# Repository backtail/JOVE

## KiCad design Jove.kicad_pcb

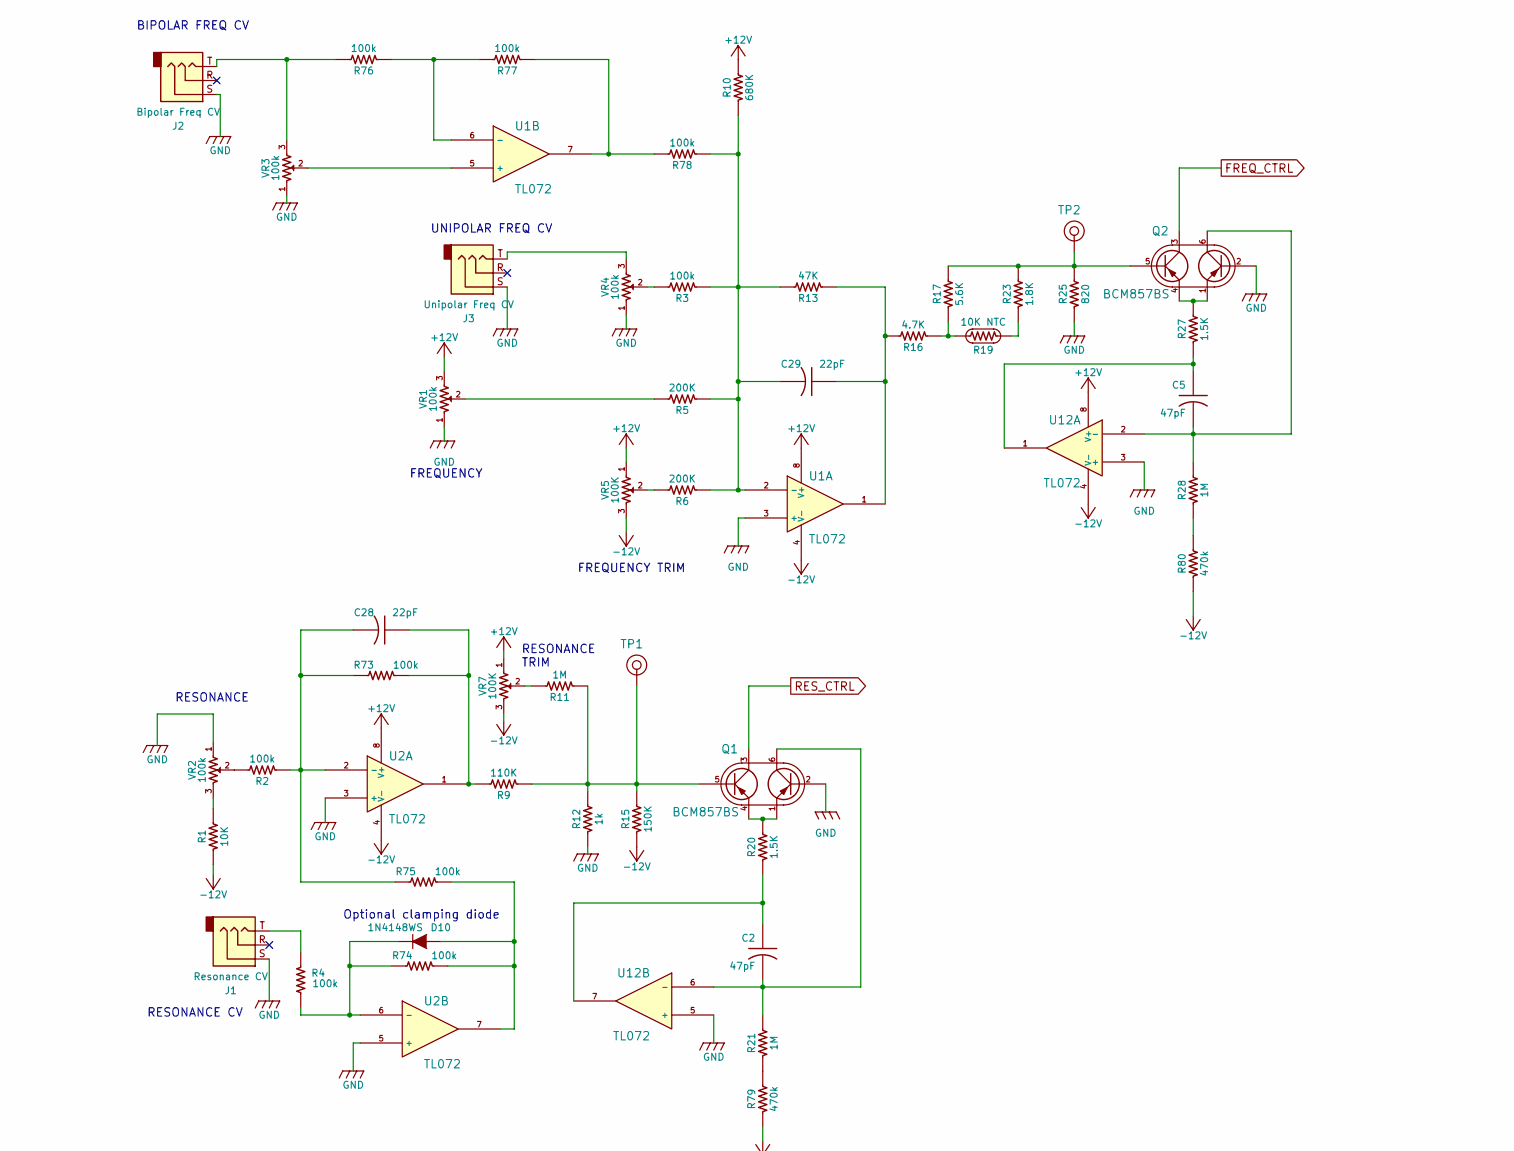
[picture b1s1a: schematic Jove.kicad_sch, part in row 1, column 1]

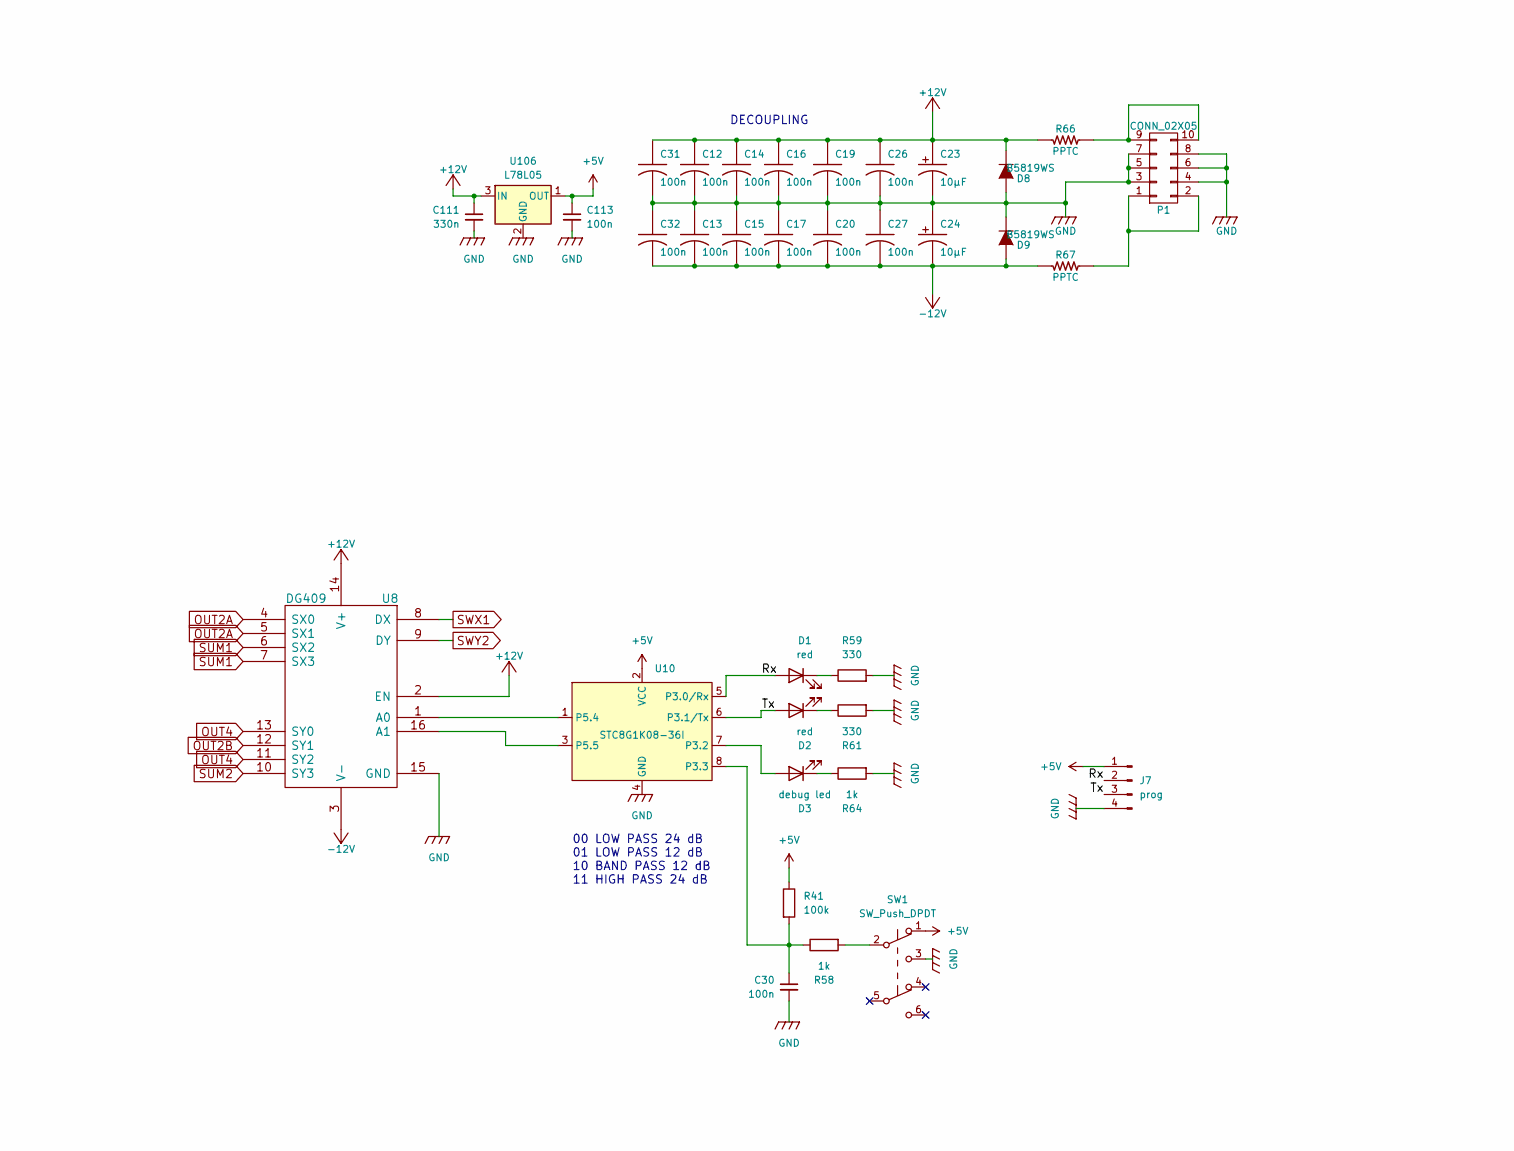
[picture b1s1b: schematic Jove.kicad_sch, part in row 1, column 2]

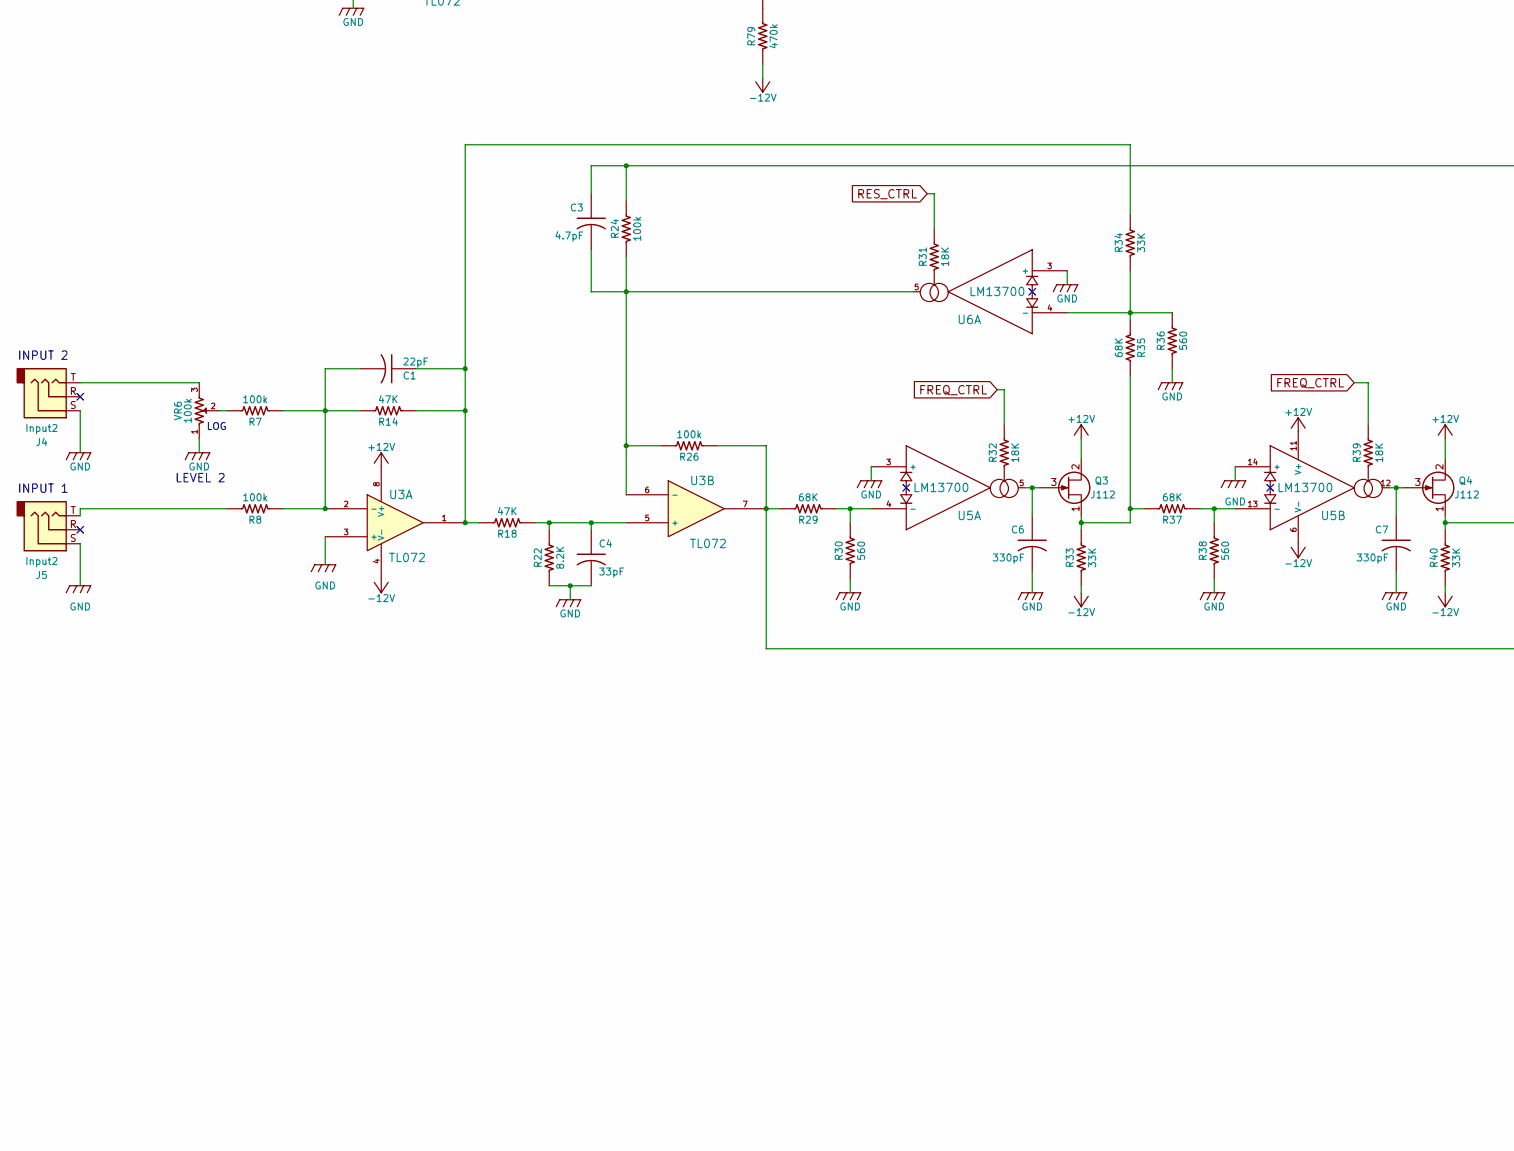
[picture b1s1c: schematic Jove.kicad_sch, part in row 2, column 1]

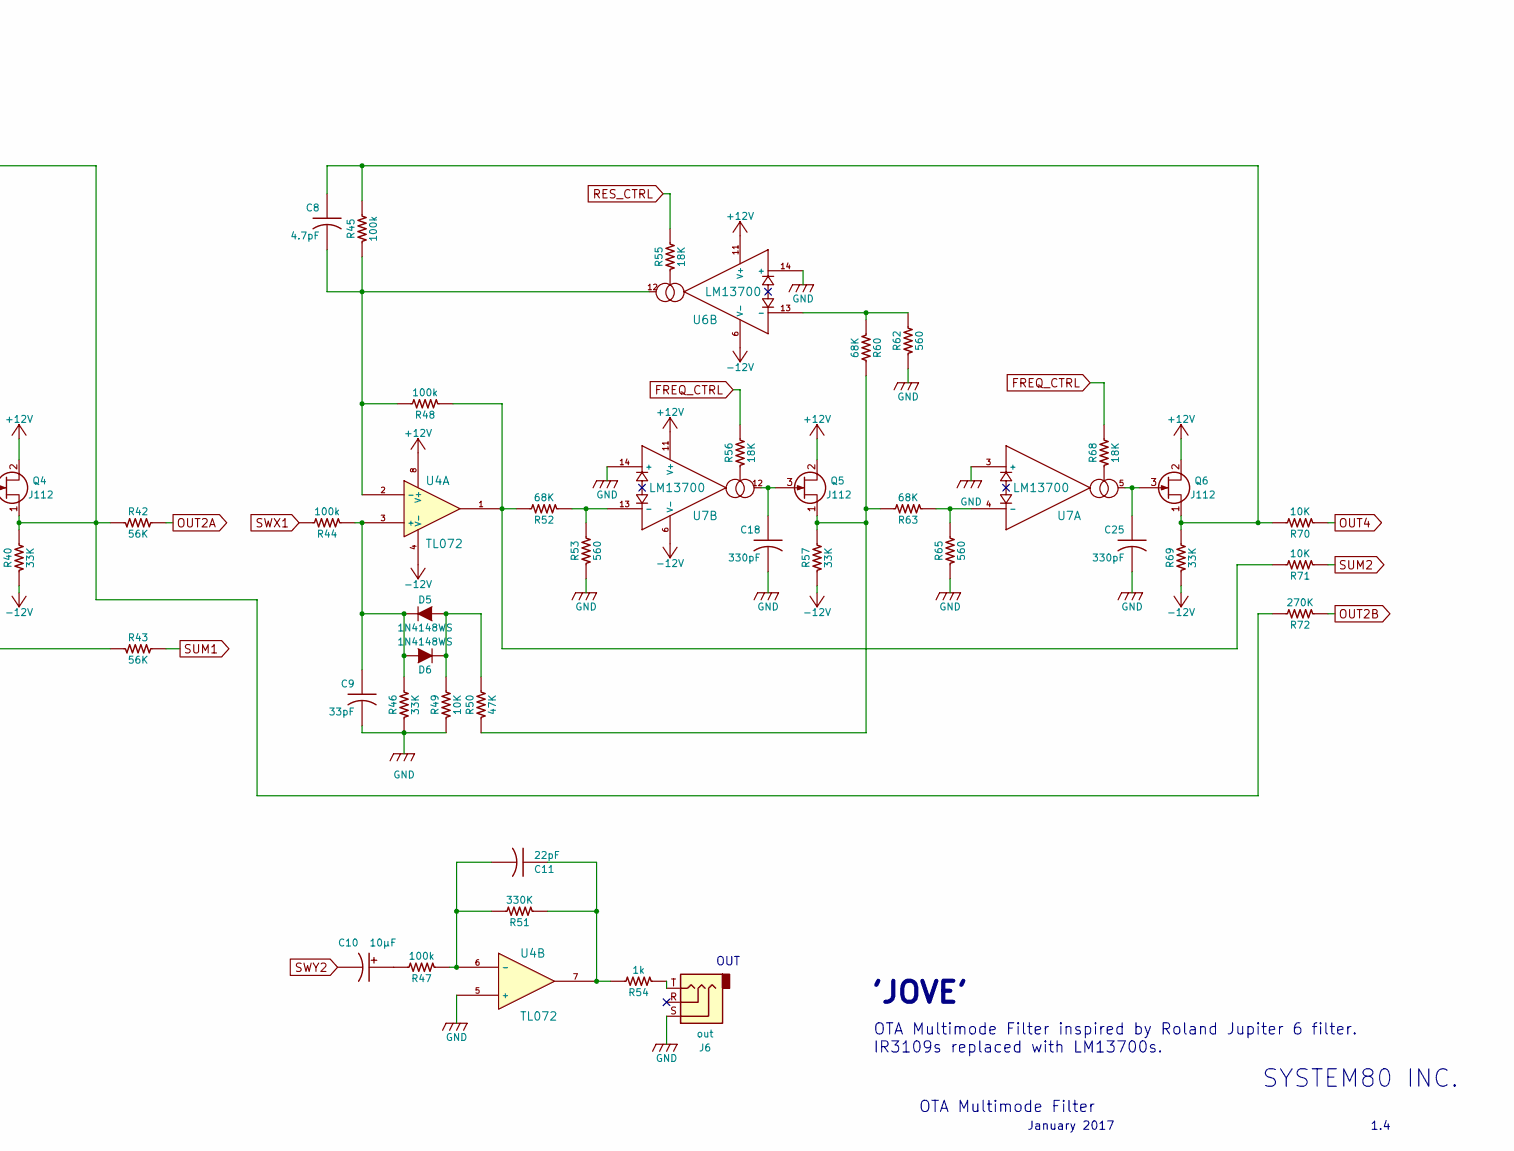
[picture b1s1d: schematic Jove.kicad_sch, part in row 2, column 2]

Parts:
C1, C11, C28, C29: 22pF; C_0603_1608Metric; LCSC Part # C1653
C2, C5: 47pF; C_0603_1608Metric; LCSC Part # C1671
C3, C8: 4.7pF; C_0603_1608Metric; LCSC Part # C1669
C4, C9: 33pF; C_0603_1608Metric; LCSC Part # C1663
C6, C7, C18, C25: 330pF; C_0603_1608Metric; LCSC Part # C1664
C10, C23, C24: 10μF; CP_EIA-3216-18_Kemet-A; LCSC Part # C7171
C12, C13, C14, C15, C16, C17, C19, C20, C26, C27, C30, C31, C32, C113: 100n; C_0402_1005Metric; LCSC Part # C1525
C111: 330n; C_0603_1608Metric; LCSC Part # C1615
D1, D2: red; LED_D1.8mm_W3.3mm_H2.4mm
D3: debug led; D_0603_1608Metric; LCSC Part # C2286
D5, D6, D10: 1N4148WS; D_SOD-323; LCSC Part # C2128
D8, D9: B5819WS; D_SOD-323; LCSC Part # C7420331
J1: Resonance CV; Jack_3.5mm_PJ392_Vertical
J2: Bipolar Freq CV; Jack_3.5mm_PJ392_Vertical
J3: Unipolar Freq CV; Jack_3.5mm_PJ392_Vertical
J4, J5: Input2; Jack_3.5mm_PJ392_Vertical
J6: out; Jack_3.5mm_PJ392_Vertical
J7: prog; PinHeader_1x04_P2.54mm_Vertical
P1: CONN_02X05; Eurorack_10Pin; LCSC Part # C5383106
Q1, Q2: BCM857BS; SOT-363_SC-70-6; LCSC Part # C105887
Q3, Q4, Q5, Q6: J112; SOT-23; LCSC Part # C258195
R1, R49, R70, R71: 10K; R_0603_1608Metric; LCSC Part # C25804
R2, R3, R4, R7, R8, R24, R26, R41, R44, R45, R47, R48, R73, R74, R75, R76, R77, R78: 100k; R_0603_1608Metric; LCSC Part # C25803
R5, R6: 200K; R_0603_1608Metric; LCSC Part # C25811
R9: 110K; R_0603_1608Metric; LCSC Part # C25805
R10: 680K; R_0603_1608Metric; LCSC Part # C25822
R11, R21, R28: 1M; R_0603_1608Metric; LCSC Part # C22935
R12, R54, R58, R64: 1k; R_0603_1608Metric; LCSC Part # C21190
R13, R14, R18, R50: 47K; R_0603_1608Metric; LCSC Part # C25819
R15: 150K; R_0603_1608Metric; LCSC Part # C22807
R16: 4.7K; R_0603_1608Metric; LCSC Part # C23162
R17: 5.6K; R_0603_1608Metric; LCSC Part # C23189
R19: 10K NTC; R_0805_2012Metric; LCSC Part # C25804
R20, R27: 1.5K; R_0603_1608Metric; LCSC Part # C22843
R22: 8.2K; R_0603_1608Metric; LCSC Part # C25981
R23: 1.8K; R_0603_1608Metric; LCSC Part # C4177
R25: 820; R_0603_1608Metric; LCSC Part # C23253
R29, R35, R37, R52, R60, R63: 68K; R_0603_1608Metric; LCSC Part # C23231
R30, R36, R38, R53, R62, R65: 560; R_0603_1608Metric; LCSC Part # C23204
R31, R32, R39, R55, R56, R68: 18K; R_0603_1608Metric; LCSC Part # C25810
R33, R34, R40, R46, R57, R69: 33K; R_0603_1608Metric; LCSC Part # C4216
R42, R43: 56K; R_0603_1608Metric; LCSC Part # C23206
R51: 330K; R_0603_1608Metric; LCSC Part # C23137
R59, R61: 330; R_0603_1608Metric; LCSC Part # C23138
R66, R67: PPTC; R_1206_3216Metric; LCSC Part # C2649905
R72: 270K; R_0603_1608Metric; LCSC Part # C22965
R79, R80: 470k; R_0603_1608Metric; LCSC Part # C23178
SW1: SW_Push_DPDT; SW_5.8x5.8mm
TP1, TP2: TEST_POINT; TestPoint_Pad_2.5x2.5mm
U1, U2, U3, U4, U12: TL072; SOIC-8_3.9x4.9mm_P1.27mm; LCSC Part # C6961
U5, U6, U7: LM13700; SOIC-16_3.9x9.9mm_P1.27mm; LCSC Part # C521166
U8: DG409; SOIC-16_3.9x9.9mm_P1.27mm; LCSC Part # C142533
U10: STC8G1K08-36I; SOIC-8_3.9x4.9mm_P1.27mm; LCSC Part # C713818
U106: L78L05; SOT-89-3; LCSC Part # C71136
VR1, VR2, VR3, VR4, VR6: 100k; Potentiometer_RK09_RV09_Vertical
VR5, VR7: 100K; Potentiometer_Bourns_TC33X_Vertical; LCSC Part # C128545

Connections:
+5V: J7.1, R41.1, SW1.1 (A), U10.2 (VCC); also elsewhere on the board
+12V: C12.1, C14.1, C16.1, C19.1, C23.1 (+), C26.1, C31.1, D8.1 (K), Q3.2 (D), Q4.2 (D), Q5.2 (D), Q6.2 (D), R10.2, R66.1, U1.8 (V+), U2.8 (V+), U3.8 (V+), U4.8 (V+), U5.11 (V+), U6.11 (V+), U7.11 (V+), U8.2 (EN), U8.14 (V+), U12.8 (V+), VR1.3, VR5.1, VR7.1; also elsewhere on the board
-12V: C13.2, C15.2, C17.2, C20.2, C24.2 (-), C27.2, C32.2, D9.2 (A), R1.2, R15.2, R33.1, R40.1, R57.1, R67.1, R69.1, R79.2, R80.2, U1.4 (V-), U2.4 (V-), U3.4 (V-), U4.4 (V-), U5.6 (V-), U6.6 (V-), U7.6 (V-), U8.3 (V-), U12.4 (V-), VR5.3, VR7.3
/Rx: D1.2 (A), J7.2, U10.5 (P3.0/Rx)
/Tx: D2.2 (A), J7.3, U10.6 (P3.1/Tx)
FREQ_CTRL: Q2.3 (C2), R32.2, R39.2, R56.2, R68.2
GND: C4.2, C6.2, C7.2, C9.2, C12.2, C13.1, C14.2, C15.1, C16.2, C17.1, C18.2, C19.2, C20.1, C23.2 (-), C24.1 (+), C25.2, C26.2, C27.1, C30.2, C31.2, C32.1, D8.2 (A), D9.1 (K), J1.S, J2.S, J3.S, J4.S, J5.S, J6.S, J7.4, P1.3, P1.4, P1.5, P1.6, P1.7, P1.8, Q1.2 (B1), Q2.2 (B1), R12.2, R22.1, R25.1, R30.1, R36.1, R38.1, R46.1, R49.1, R53.1, R59.2, R61.2, R62.1, R64.2, R65.1, SW1.3 (C), U1.3 (+), U2.3 (+), U2.5 (+), U3.3 (+), U4.5 (+), U5.3 (+), U5.14 (+), U6.3 (+), U6.14 (+), U7.3 (+), U7.14 (+), U8.15 (GND), U10.4 (GND), U12.3 (+), U12.5 (+), VR1.1, VR2.1, VR3.1, VR4.1, VR6.1; also elsewhere on the board
unnamed: C1.1, R14.1, R18.2, R34.2, U3.1
unnamed: C2.1, R20.2, U12.7
unnamed: C5.1, R27.2, U12.1
unnamed: C10.1 (+), R47.2
unnamed: C11.1, R51.1, R54.2, U4.7
unnamed: C28.1, R9.2, R73.1, U2.1
unnamed: C29.1, R13.1, R16.2, U1.1
unnamed: D1.1 (K), R59.1
unnamed: D2.1 (K), R61.1
unnamed: D3.2 (A), U10.7 (P3.2)
unnamed: D3.1 (K), R64.1
unnamed: D5.2 (A), D6.1 (K), R49.2, R50.2
unnamed: C9.1, D5.1 (K), D6.2 (A), R44.1, R46.2, U4.3 (+)
unnamed: D10.2 (A), R74.1, R75.1, U2.7
unnamed: D10.1 (K), R4.1, R74.2, U2.6 (-)
unnamed: J1.T, R4.2
unnamed: J2.T, R76.2, VR3.3
unnamed: J3.T, VR4.3
unnamed: J4.T, VR6.3
unnamed: J5.T, R8.2
unnamed: J6.T, R54.1
unnamed: P1.1, P1.2, R67.2
unnamed: P1.9, P1.10, R66.2
unnamed: Q1.5 (B2), R9.1, R11.1, R12.1, R15.1, TP1.1
unnamed: C2.2, Q1.6 (C1), R21.1, U12.6 (-)
unnamed: Q1.1 (E1), Q1.4 (E2), R20.1
unnamed: Q2.5 (B2), R17.2, R23.2, R25.2, TP2.1
unnamed: C5.2, Q2.6 (C1), R28.1, U12.2 (-)
unnamed: Q2.1 (E1), Q2.4 (E2), R27.1
unnamed: C6.1, Q3.3 (G), U5.5
unnamed: Q3.1 (S), R33.2, R35.2, R37.2
unnamed: C7.1, Q4.3 (G), U5.12
unnamed: C3.1, Q4.1 (S), R24.2, R40.2, R42.2, R72.2
unnamed: C18.1, Q5.3 (G), U7.12
unnamed: Q5.1 (S), R50.1, R57.2, R60.2, R63.2
unnamed: C25.1, Q6.3 (G), U7.5
unnamed: C8.1, Q6.1 (S), R45.2, R69.2, R70.2
unnamed: R1.1, VR2.3
unnamed: R2.2, VR2.2
unnamed: R3.2, VR4.2
unnamed: R5.2, VR1.2
unnamed: R6.2, VR5.2
unnamed: R7.2, VR6.2
unnamed: R11.2, VR7.2
unnamed: R16.1, R17.1, R19.2
unnamed: R19.1, R23.1
unnamed: R21.2, R79.1
unnamed: R26.1, R29.2, R43.2, U3.7
unnamed: R28.2, R80.1
unnamed: R31.1, U6.1
unnamed: R32.1, U5.1
unnamed: R39.1, U5.16
unnamed: R48.1, R52.2, R71.2, U4.1
unnamed: R55.1, U6.16
unnamed: R56.1, U7.16
unnamed: R58.2, SW1.2 (B)
unnamed: R68.1, U7.1
unnamed: R77.1, R78.2, U1.7
unnamed: C29.2, R3.1, R5.1, R6.1, R10.1, R13.2, R78.1, U1.2 (-)
unnamed: U1.5 (+), VR3.2
unnamed: R76.1, R77.2, U1.6 (-)
unnamed: C28.2, R2.1, R73.2, R75.2, U2.2 (-)
unnamed: C1.2, R7.1, R8.1, R14.2, U3.2 (-)
unnamed: C4.1, R18.1, R22.2, U3.5 (+)
unnamed: C3.2, R24.1, R26.2, U3.6 (-), U6.5
unnamed: C8.2, R45.1, R48.2, U4.2 (-), U6.12
unnamed: C11.2, R47.1, R51.2, U4.6 (-)
unnamed: R29.1, R30.2, U5.4 (-)
unnamed: R37.1, R38.2, U5.13 (-)
unnamed: R34.1, R35.1, R36.2, U6.4 (-)
unnamed: R60.1, R62.2, U6.13 (-)
unnamed: R63.1, R65.2, U7.4 (-)
unnamed: R52.1, R53.2, U7.13 (-)
unnamed: C30.1, R41.2, R58.1, U10.8 (P3.3)
unnamed: U8.1 (A0), U10.1 (P5.4)
unnamed: U8.16 (A1), U10.3 (P5.5)
OUT2A: R42.1, U8.4 (SX0), U8.5 (SX1)
OUT2B: R72.1, U8.12 (SY1)
OUT4: R70.1, U8.11 (SY2), U8.13 (SY0)
RES_CTRL: Q1.3 (C2), R31.2, R55.2
SUM1: R43.1, U8.6 (SX2), U8.7 (SX3)
SUM2: R71.1, U8.10 (SY3)
SWX1: R44.2, U8.8 (DX)
SWY2: C10.2 (-), U8.9 (DY)

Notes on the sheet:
DECOUPLING
OUT
'JOVE'
BIPOLAR FREQ CV
OTA Multimode Filter
UNIPOLAR FREQ CV
LOG
RESONANCE CV
LEVEL 2
1.4
Optional clamping diode
FREQUENCY
RESONANCE
00 LOW PASS 24 dB 01 LOW PASS 12 dB 10 BAND PASS 12 dB 11 HIGH PASS 24 dB
OTA Multimode Filter inspired by Roland Jupiter 6 filter. IR3109s replaced with LM13700s.
RESONANCE TRIM
FREQUENCY TRIM
January 2017
INPUT 1
INPUT 2
SYSTEM80 INC.

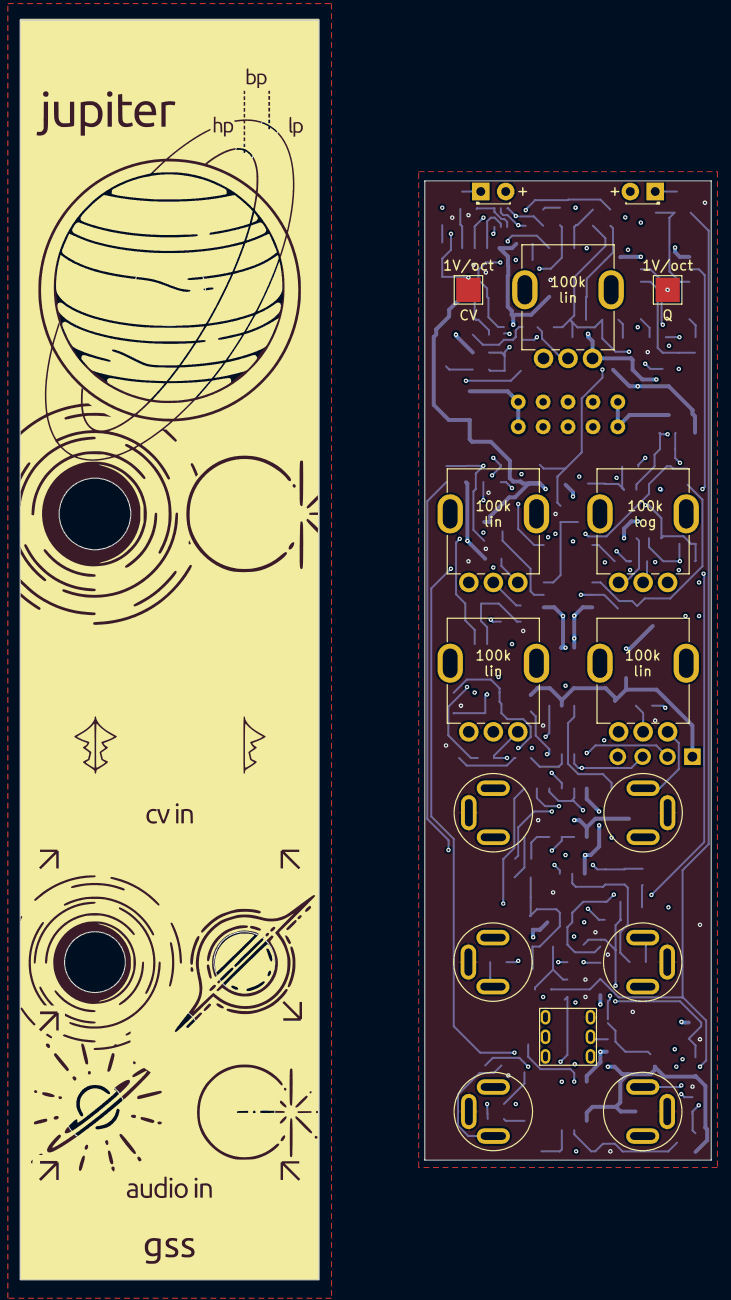
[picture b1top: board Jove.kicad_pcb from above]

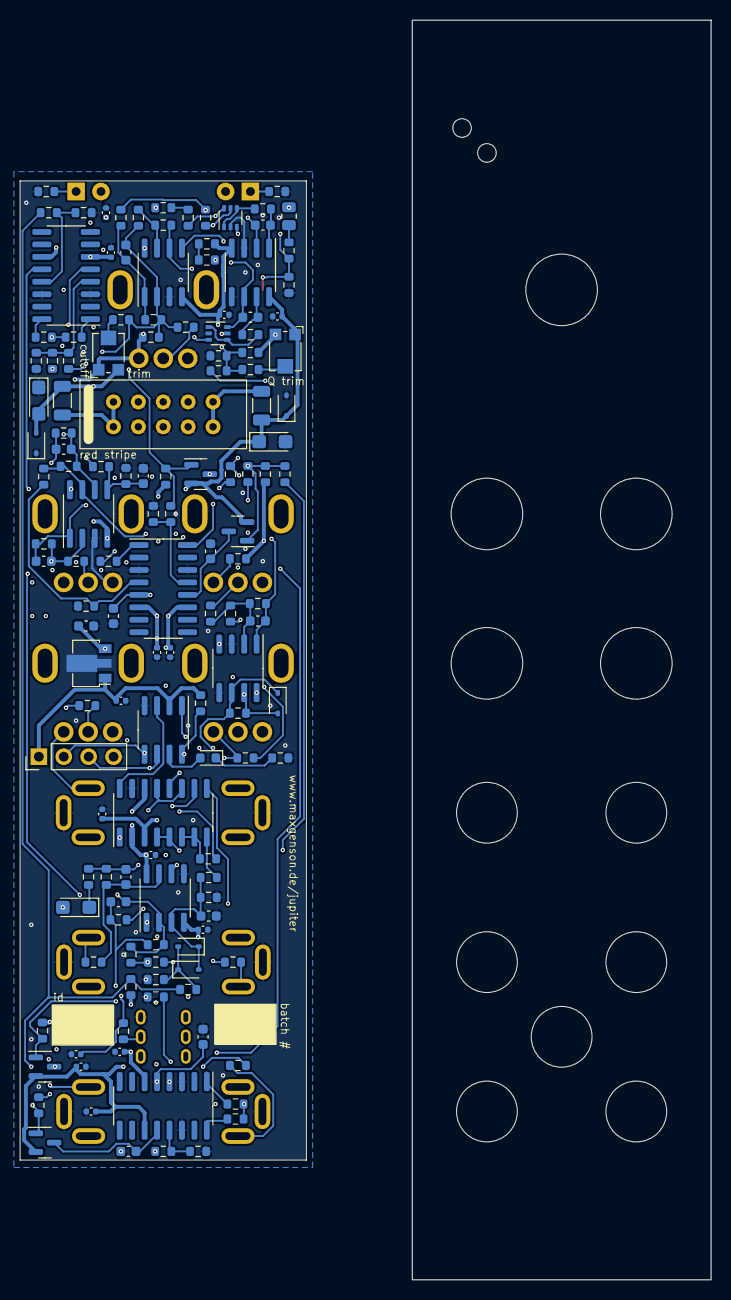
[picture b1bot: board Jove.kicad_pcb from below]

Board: 4 copper layers, 29.2 x 99.9 mm, 155 parts (139 on the bottom side), 91 nets.

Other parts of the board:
C21: 330n; C_0603_1608Metric
C22: 100n; C_0402_1005Metric
U9: L78L05; SOT-89-3

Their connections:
+5V: C22.1, U9.1 (OUT); also elsewhere on the board
+12V: C21.1, U9.3 (IN); also elsewhere on the board
GND: C21.2, C22.2, U9.2 (GND); also elsewhere on the board

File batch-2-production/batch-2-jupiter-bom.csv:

Designator,Footprint,Quantity,Value,LCSC Part #
"C1, C11, C28, C29",0603,4,22pF,C1653
"C10, C23, C24",CP_EIA-3216-18_Kemet-A,3,10μF,C7171
"C12, C13, C14, C15, C16, C17, C19, C20, C22, C26, C27, C30, C31, C32",0402,14,100n,C1525 
"C18, C25, C6, C7",0603,4,330pF,C1664
"C2, C5",0603,2,47pF,C1671
C21,0603,1,330n,C1615
"C3, C8",0603,2,4.7pF,C1669
"C4, C9",0603,2,33pF,C1663
"D1, D2",LED_D1.8mm_W3.3mm_H2.4mm,2,red,
"D10, D5, D6",D_SOD-323,3,1N4148WS,C2128
D3,0603,1,debug led,C2286
"D8, D9",D_SOD-323,2,B5819WS,C7420331
J1,Jack_3.5mm_PJ392_Vertical,1,Resonance CV,
J2,Jack_3.5mm_PJ392_Vertical,1,Bipolar Freq CV,
J3,Jack_3.5mm_PJ392_Vertical,1,Unipolar Freq CV,
"J4, J5",Jack_3.5mm_PJ392_Vertical,2,Input2,
J6,Jack_3.5mm_PJ392_Vertical,1,out,
J7,PinHeader_1x04_P2.54mm_Vertical,1,prog,
P1,Eurorack_10Pin,1,CONN_02X05,C5383106
"Q1, Q2",SOT-363_SC-70-6,2,BCM857BS,C105887
"Q3, Q4, Q5, Q6",SOT-23,4,J112,C258195
"R1, R49, R70, R71",0603,4,10K,C25804
R10,0603,1,680K,C25822
"R11, R21, R28",0603,3,1M,C22935
"R12, R54, R58, R64",0603,4,1k,C21190
"R13, R14, R18, R50",0603,4,47K,C25819
R15,0603,1,150K,C22807
R16,0603,1,4.7K,C23162
R17,0603,1,5.6K,C23189
R19,0805,1,10K NTC,C25804
"R2, R24, R26, R3, R4, R41, R44, R45, R47, R48, R7, R73, R74, R75, R76, R77, R78, R8",0603,18,100k,C25803
"R20, R27",0603,2,1.5K,C22843
R22,0603,1,8.2K,C25981
R23,0603,1,1.8K,C4177
R25,0603,1,820,C23253
"R29, R35, R37, R52, R60, R63",0603,6,68K,C23231
"R30, R36, R38, R53, R62, R65",0603,6,560,C23204
"R31, R32, R39, R55, R56, R68",0603,6,18K,C25810
"R33, R34, R40, R46, R57, R69",0603,6,33K,C4216
"R42, R43",0603,2,56K,C23206
"R5, R6",0603,2,200K,C25811
R51,0603,1,330K,C23137
"R59, R61",0603,2,330,C23138
"R66, R67",1206,2,PPTC,C2649905
R72,0603,1,270K,C22965
"R79, R80",0603,2,470k,C23178
R9,0603,1,110K,C25805
SW1,SW_5.8x5.8mm,1,SW_Push_DPDT,
"TP1, TP2",TestPoint_Pad_2.5x2.5mm,2,TEST_POINT,
"U1, U12, U2, U3, U4",SOIC-8_3.9x4.9mm_P1.27mm,5,TL072,C6961
U10,SOIC-8_3.9x4.9mm_P1.27mm,1,STC8G1K08-36I,C713818
"U5, U6, U7",SOIC-16_3.9x9.9mm_P1.27mm,3,LM13700,C521166
U8,SOIC-16_3.9x9.9mm_P1.27mm,1,DG409,C142533
U9,SOT-89-3,1,L78L05,C71136
"VR1, VR2, VR3, VR4, VR6",Potentiometer_RK09_RV09_Vertical,5,100k,
"VR5, VR7",Potentiometer_Bourns_TC33X_Vertical,2,100K,C128545

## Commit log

2024-02-12 redesign PCB
2024-02-12 redesign Frontpanel
2024-02-12 add gerbers
2024-02-12 first firmware
2024-02-19 fw 1.0
2024-02-19 update frontpanel design to fit eurorack cases
2024-02-20 cleanup
2024-02-20 add STC8 HAL as submodule
2024-02-21 ordered fixed frontpanels
2024-10-23 add batch 2 changes
